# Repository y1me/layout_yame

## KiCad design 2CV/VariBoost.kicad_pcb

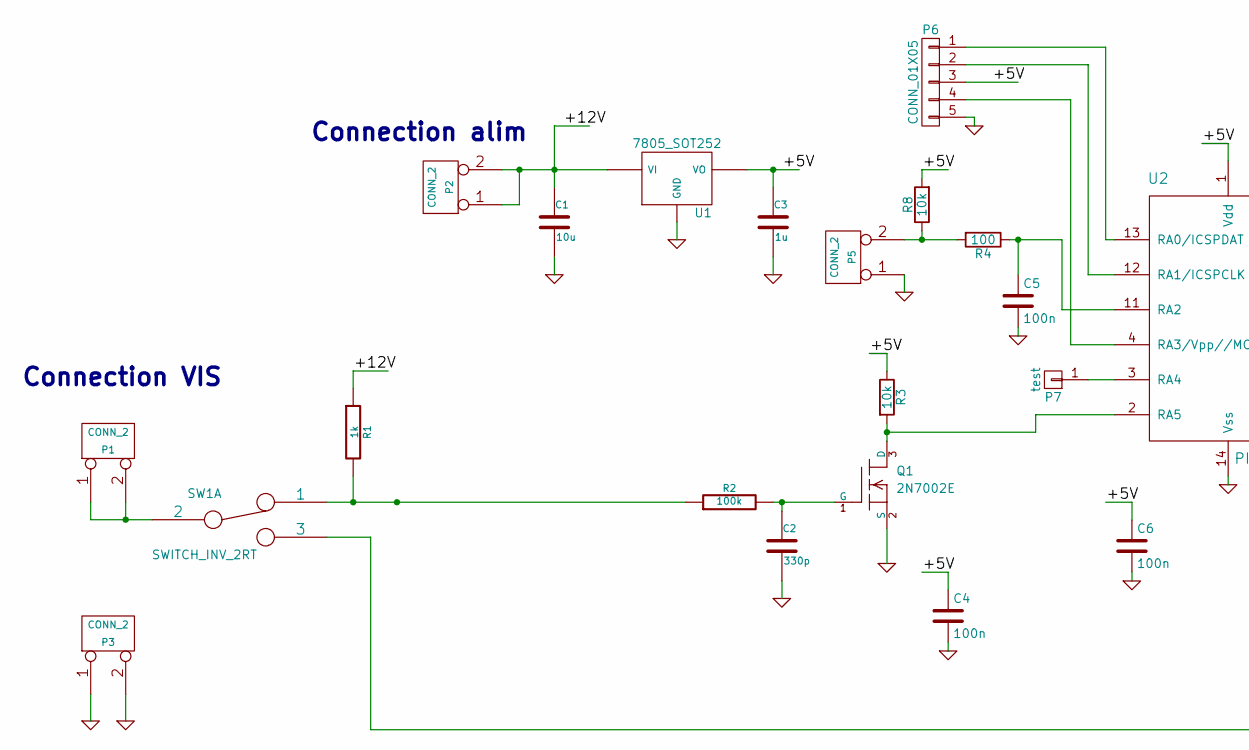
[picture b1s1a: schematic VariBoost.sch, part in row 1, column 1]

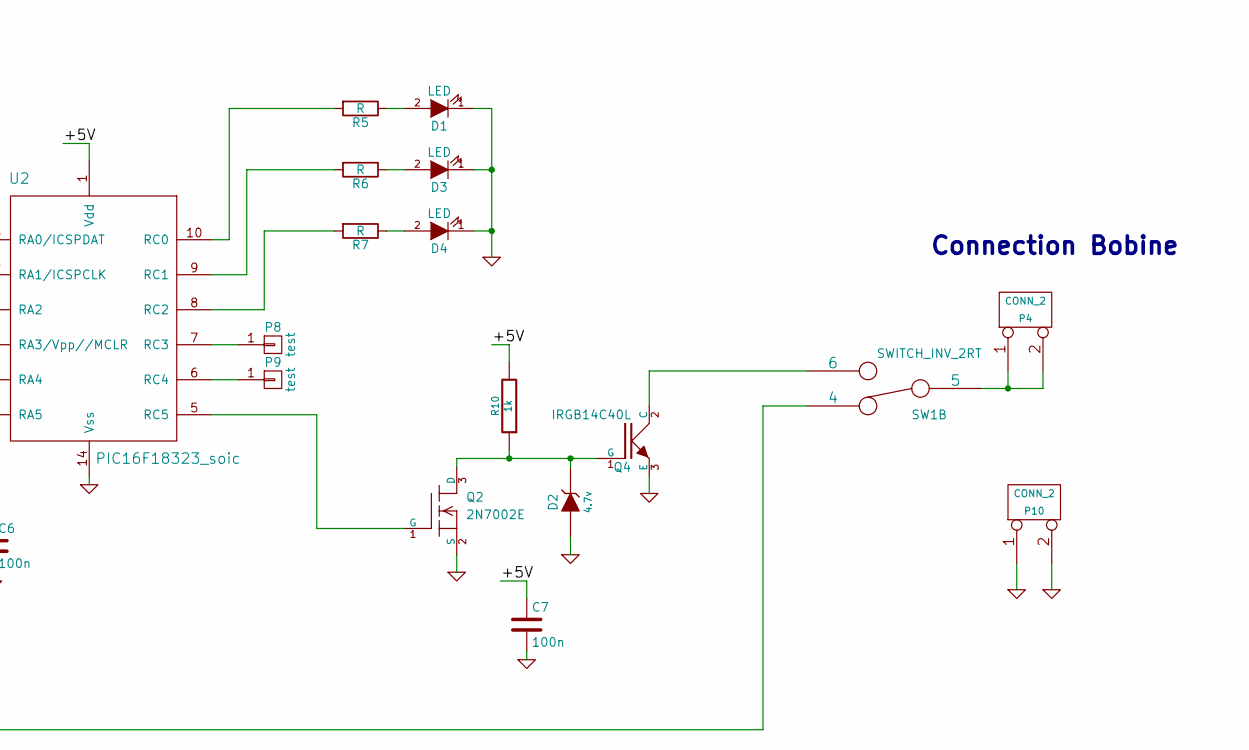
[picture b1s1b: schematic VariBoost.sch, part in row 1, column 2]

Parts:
C1: 10u; SM0805-MR
C2: 330p; SM0603-MR
C3: 1u; SM0603-MR
C4, C5, C6, C7: 100n; SM0603-MR
D1, D3, D4: LED; SM0603-LED-MR
D2: 4.7v; SOD-123
P1, P2, P3, P4, P5, P10: CONN_2; bornier2
P6: CONN_01X05; HE10_14-5C-2.54-MR
P7, P8, P9: test; Test_Point_T_H
Q1, Q2: 2N7002E; SOT23-MR
Q4: IRGB14C40L; TO-220_Neutral123_Vertical_LargePads
R1, R10: 1k; SM0603-MR
R2: 100k; SM0603-MR
R3, R8: 10k; SM0603-MR
R4: 100; SM0603-MR
R5, R6, R7: R; SM0603-MR
SW1: SWITCH_INV_2RT; SW_DPDT_2RT_5_08
U1: 7805_SOT252; TO-252-2Lead
U2: PIC16F18323_soic; SOIC-14_3.9x8.7mm_Pitch1.27mm

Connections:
/+5V: C3.1, C4.1, C6.1, C7.1, P6.3, R3.1, R8.2, R10.2, U1.3 (VO), U2.1 (Vdd)
/+12V: C1.1, P2.1, P2.2 (PM), R1.1, U1.1 (VI)
GND: C1.2, C2.2, C3.2, C4.2, C5.2, C6.2, C7.2, D1.1 (K), D2.1 (A), D3.1 (K), D4.1 (K), P3.1, P3.2 (PM), P5.1, P6.5, P10.1, P10.2 (PM), Q1.2 (S), Q2.2 (S), Q4.3 (E), U1.2 (GND), U2.14 (Vss); also elsewhere on the board
unnamed: C2.1, Q1.1 (G), R2.2
unnamed: C5.1, R4.1, U2.11 (RA2)
unnamed: D1.2 (A), R5.1
unnamed: D2.2 (K), Q2.3 (D), Q4.1 (G), R10.1
unnamed: D3.2 (A), R6.1
unnamed: D4.2 (A), R7.1
unnamed: P1.1, P1.2 (PM), SW1.2
unnamed: P4.1, P4.2 (PM), SW1.5
unnamed: P5.2 (PM), R4.2, R8.1
unnamed: P6.1, U2.13 (RA0/ICSPDAT)
unnamed: P6.2, U2.12 (RA1/ICSPCLK)
unnamed: P6.4, U2.4 (RA3/Vpp//MCLR)
unnamed: P7.1, U2.3 (RA4)
unnamed: P8.1, U2.7 (RC3)
unnamed: P9.1, U2.6 (RC4)
unnamed: Q1.3 (D), R3.2, U2.2 (RA5)
unnamed: Q2.1 (G), U2.5 (RC5)
unnamed: Q4.2 (C), SW1.6
unnamed: R1.2, R2.1, SW1.1
unnamed: R5.2, U2.10 (RC0)
unnamed: R6.2, U2.9 (RC1)
unnamed: R7.2, U2.8 (RC2)
unnamed: SW1.3, SW1.4

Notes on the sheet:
Connection alim
Connection VIS
Connection Bobine

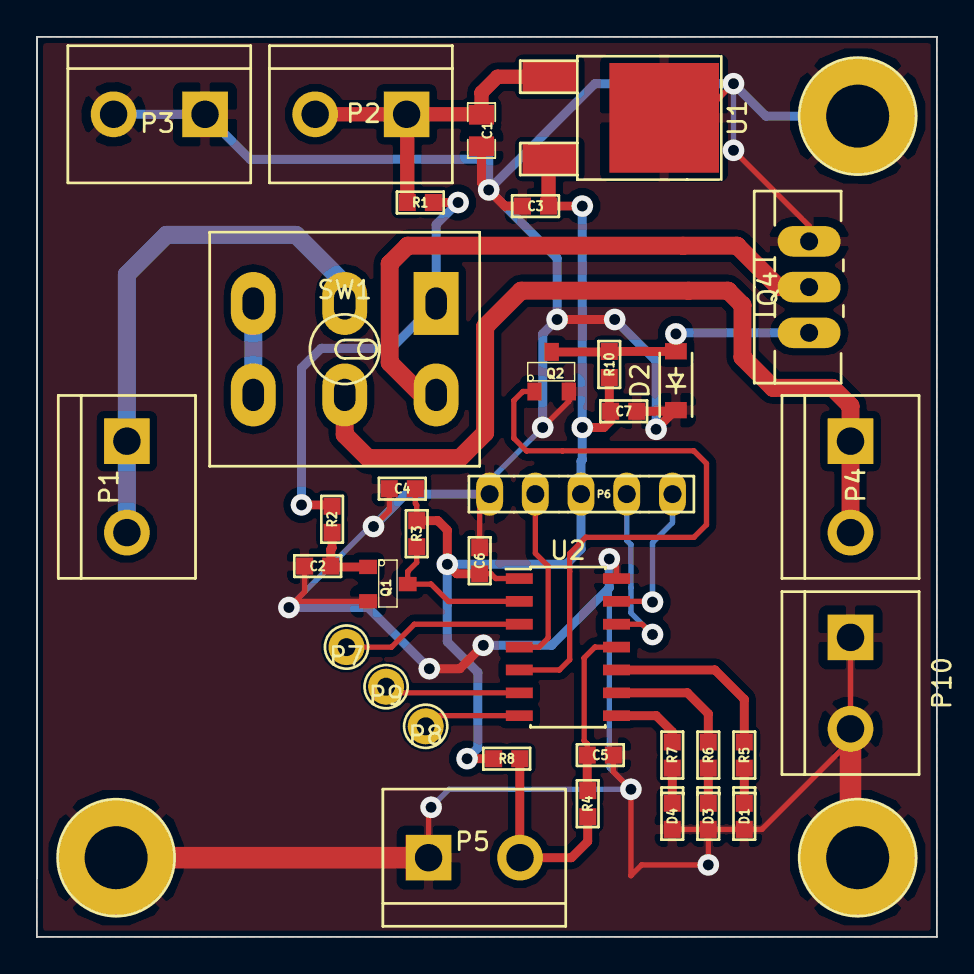
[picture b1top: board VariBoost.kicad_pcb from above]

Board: 2 copper layers, 50.0 x 50.0 mm, 39 parts (0 on the bottom side), 26 nets.

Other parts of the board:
MountingHole_3.5-6.5+GND, MountingHole_3.5-6.5+GND#2, MountingHole_3.5-6.5+GND#3: VAL**; MountingHole_3.5-6.5_GND

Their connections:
GND: MountingHole_3.5-6.5+GND.1, MountingHole_3.5-6.5+GND#2.1, MountingHole_3.5-6.5+GND#3.1; also elsewhere on the board

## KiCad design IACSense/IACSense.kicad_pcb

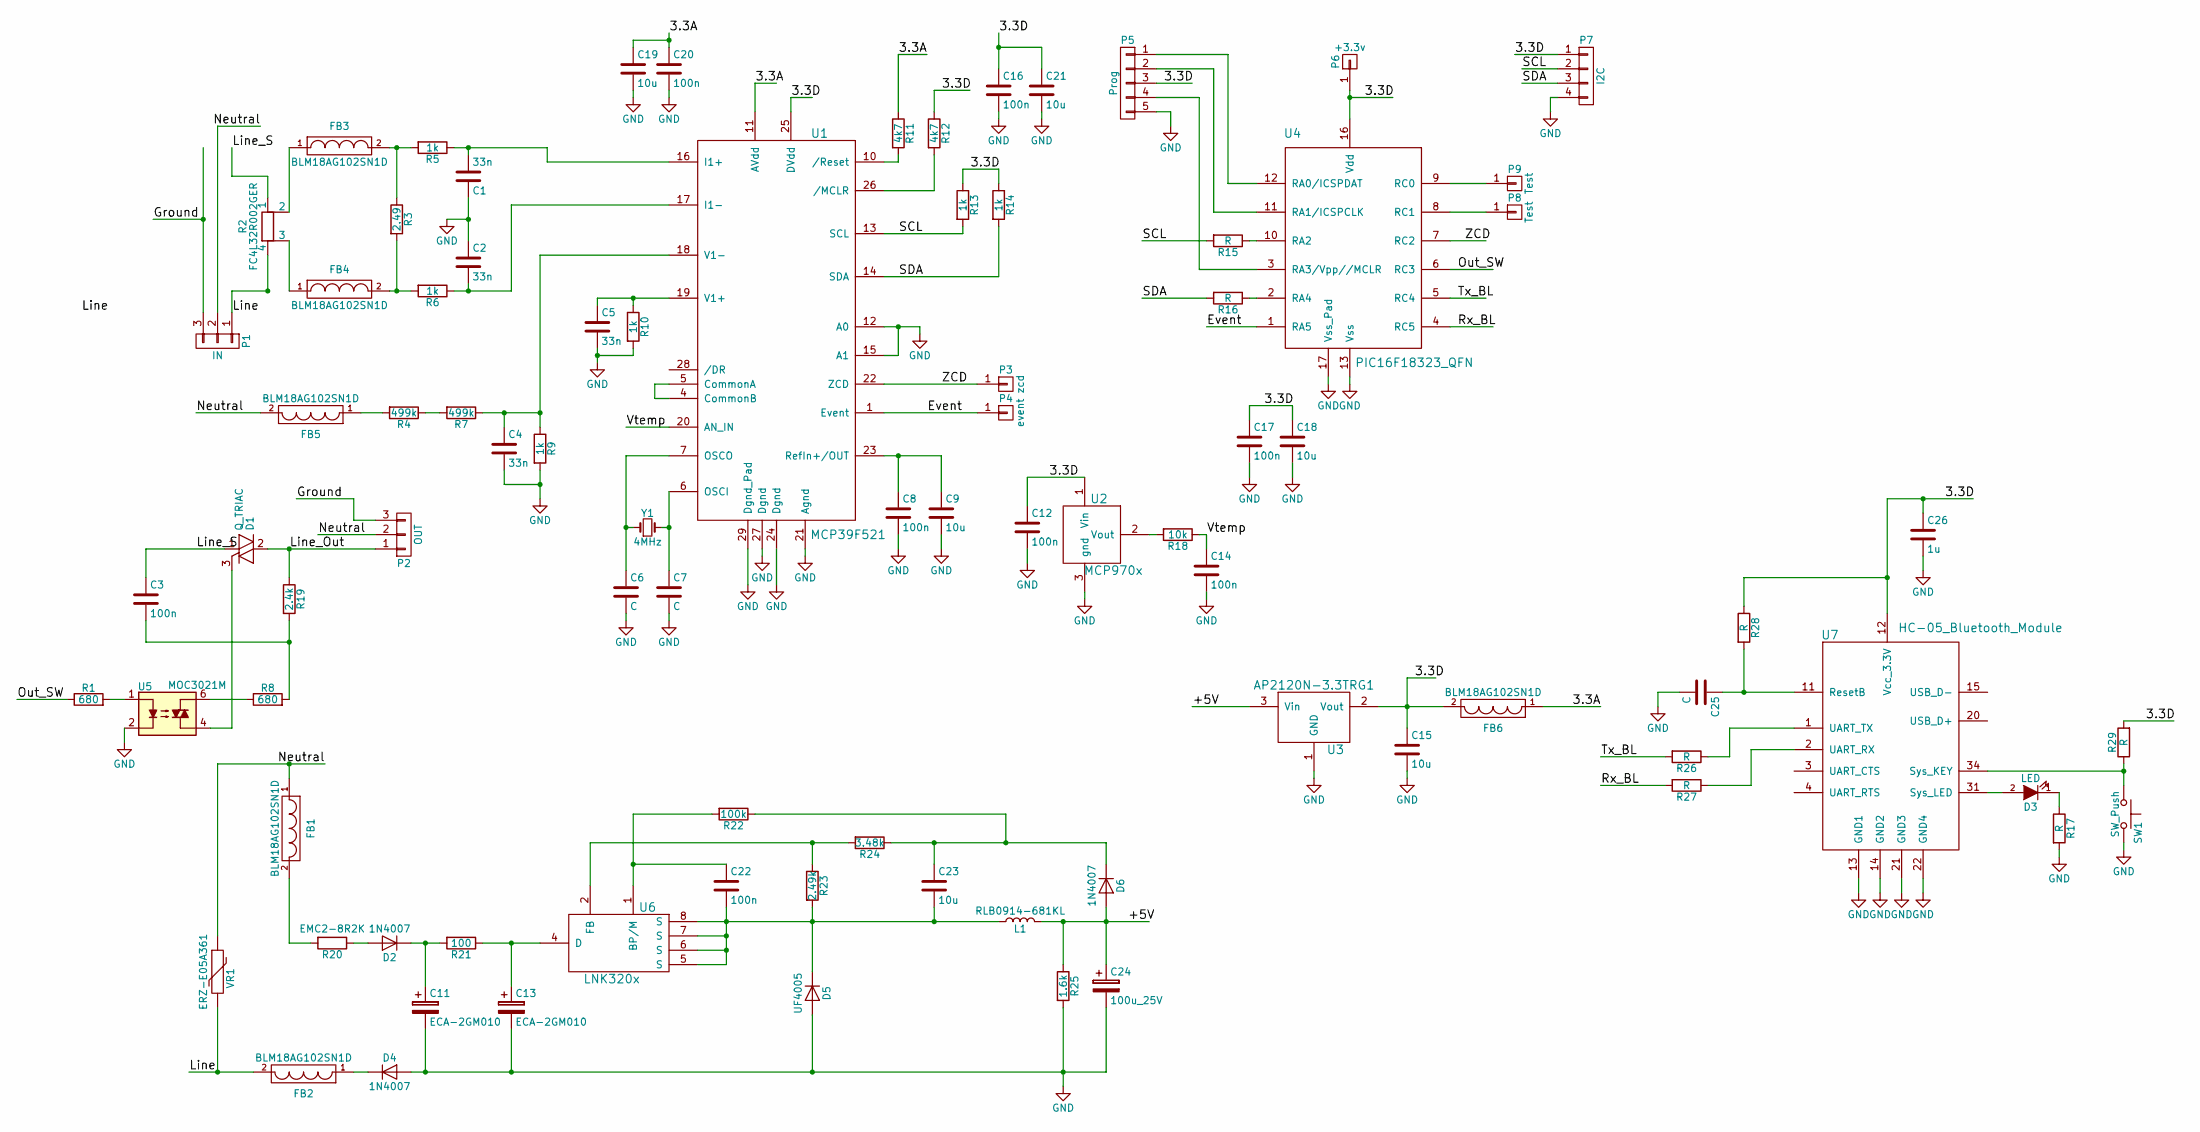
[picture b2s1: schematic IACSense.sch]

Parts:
C1, C2, C4, C5: 33n; SM0603-MR
C3: 100n; C_Rect_L13.0mm_W6.0mm_P10.00mm_FKS3_FKP3_MKS4
C6, C7, C25: C; SM0603-MR
C8, C12, C14, C16, C17, C20, C22: 100n; SM0603-MR
C9, C15, C18, C19, C21, C23: 10u; SM0805-MR
C11, C13: ECA-2GM010; CP_Radial_D6.3mm_P2.50mm
C24: 100u_25V; CP_Radial_D6.3mm_P2.50mm
C26: 1u; SM0805-MR
D1: Q_TRIAC; TO-220-3_Vertical
D2, D4, D6: 1N4007; D_DO-41_SOD81_P7.62mm_Horizontal
D3: LED; SM0603-LED-MR
D5: UF4005; D_DO-41_SOD81_P7.62mm_Horizontal
FB1, FB2, FB3, FB4, FB5, FB6: BLM18AG102SN1D; SM0603-MR
L1: RLB0914-681KL; L_Radial_D8.7mm_P5.00mm_Fastron_07HCP
P1: IN; Conn3_Term
P2: OUT; Conn3_Term
P3: zcd; Pin_Header_Straight_1x01_Pitch1.00mm
P4: event; Pin_Header_Straight_1x01_Pitch1.00mm
P5: Prog; Pin_Header_Straight_1x05_Pitch2.54mm
P6: +3.3v; Pin_Header_Straight_1x01_Pitch1.00mm
P7: I2C; Pin_Header_Straight_1x04_Pitch1.27mm
P8, P9: Test; Pin_Header_Straight_1x01_Pitch1.00mm
R1: 680; SM0603-MR
R2: FC4L32R002GER; FC4L32
R3: 2.49; SM0603-MR
R4, R7: 499k; SM0603-MR
R5, R6, R9, R10, R13, R14: 1k; SM0603-MR
R8: 680; R_Axial_DIN0414_L11.9mm_D4.5mm_P5.08mm_Vertical
R11, R12: 4k7; SM0603-MR
R15, R16: R; SM0201-MR
R17, R26, R27, R28, R29: R; SM0603-MR
R18: 10k; SM0603-MR
R19: 2.4k; R_Axial_DIN0414_L11.9mm_D4.5mm_P5.08mm_Vertical
R20: EMC2-8R2K; R_Axial_DIN0414_L11.9mm_D4.5mm_P5.08mm_Vertical
R21: 100; SM0805-MR
R22: 100k; SM0603-MR
R23: 2.49k; SM0603-MR
R24: 3.48k; SM0603-MR
R25: 1.6k; SM0603-MR
SW1: SW_Push; SW_SPST_FSMSM
U1: MCP39F521; QFN-28-1EP_5x5mm_Pitch0.5mm
U2: MCP970x; SOT23-MR
U3: AP2120N-3.3TRG1; SOT23-MR
U4: PIC16F18323_QFN; QFN-16-1EP_4x4mm_Pitch0.65mm
U5: MOC3021M; DIP-6_W7.62mm
U6: LNK320x; SO-8C-7
U7: HC-05_Bluetooth_Module; HM-10_BLE
VR1: ERZ-E05A361; VR_5mm
Y1: 4MHz; Crystal_HC49-4H_Vertical

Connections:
/3.3A: C19.1, C20.1, FB6.1, R11.1, U1.11 (AVdd)
/3.3D: C12.1, C15.1, C16.1, C17.1, C18.1, C21.1, C26.1, FB6.2, P5.3, P6.1, P7.1, R12.1, R13.1, R14.1, R28.1, R29.2, U1.25 (DVdd), U2.1 (Vin), U3.2 (Vout), U4.16 (Vdd), U7.12 (Vcc_3.3V)
/+5V: C24.1, D6.2 (A), L1.2, R25.1, U3.3 (Vin)
/Event: P4.1, U1.1 (Event), U4.1 (RA5)
/Ground: P1.3, P2.3
/Line: FB2.2, P1.1, R2.4, VR1.2
/Line_Out: D1.2 (A1), P2.1, R19.1
/Line_S: C3.1, D1.1 (A2), R2.1
/Neutral: FB1.1, FB5.2, P1.2, P2.2, VR1.1
/Out_SW: R1.1, U4.6 (RC3)
/Rx_BL: R27.2, U4.4 (RC5)
/SCL: P7.2, R13.2, R15.2, U1.13 (SCL)
/SDA: P7.3, R14.2, R16.2, U1.14 (SDA)
/Tx_BL: R26.2, U4.5 (RC4)
/Vtemp: C14.1, R18.1, U1.20 (AN_IN)
/ZCD: P3.1, U1.22 (ZCD), U4.7 (RC2)
GND: C1.1, C2.1, C4.2, C5.2, C6.2, C7.2, C8.2, C9.2, C11.2, C12.2, C13.2, C14.2, C15.2, C16.2, C17.2, C18.2, C19.2, C20.2, C21.2, C24.2, C25.2, C26.2, D4.2 (A), D5.2 (A), P5.5, P7.4, R9.2, R10.2, R17.2, R25.2, SW1.2, U1.12 (A0), U1.15 (A1), U1.21 (Agnd), U1.24 (Dgnd), U1.27 (Dgnd), U1.29 (Dgnd_Pad), U2.3 (gnd), U3.1 (GND), U4.13 (Vss), U4.17 (Vss_Pad), U5.2, U7.13 (GND1), U7.14 (GND2), U7.21 (GND3), U7.22 (GND4)
unnamed: C1.2, R5.1, U1.16 (I1+)
unnamed: C2.2, R6.1, U1.17 (I1-)
unnamed: C3.2, R8.2, R19.2
unnamed: C4.1, R7.1, R9.1, U1.18 (V1-)
unnamed: C5.1, R10.1, U1.19 (V1+)
unnamed: C6.1, U1.7 (OSCO), Y1.1
unnamed: C7.1, U1.6 (OSCI), Y1.2
unnamed: C8.1, C9.1, U1.23 (RefIn+/OUT)
unnamed: C11.1, D2.1 (K), R21.2
unnamed: C13.1, R21.1, U6.4 (D)
unnamed: C22.1, R22.2, U6.1 (BP/M)
unnamed: C22.2, C23.2, D5.1 (K), L1.1, R23.2, U6.5 (S), U6.6 (S), U6.7 (S), U6.8 (S)
unnamed: C23.1, D6.1 (K), R22.1, R24.1
unnamed: C25.1, R28.2, U7.11 (ResetB)
unnamed: D1.3 (G), U5.4
unnamed: D2.2 (A), R20.1
unnamed: D3.1 (K), R17.1
unnamed: D3.2 (A), U7.31 (Sys_LED)
unnamed: D4.1 (K), FB2.1
unnamed: FB1.2, R20.2
unnamed: FB3.1, R2.2
unnamed: FB3.2, R3.1, R5.2
unnamed: FB4.1, R2.3
unnamed: FB4.2, R3.2, R6.2
unnamed: FB5.1, R4.2
unnamed: P5.1, U4.12 (RA0/ICSPDAT)
unnamed: P5.2, U4.11 (RA1/ICSPCLK)
unnamed: P5.4, U4.3 (RA3/Vpp//MCLR)
unnamed: P8.1, U4.8 (RC1)
unnamed: P9.1, U4.9 (RC0)
unnamed: R1.2, U5.1
unnamed: R4.1, R7.2
unnamed: R8.1, U5.6
unnamed: R11.2, U1.10 (/Reset)
unnamed: R12.2, U1.26 (/MCLR)
unnamed: R15.1, U4.10 (RA2)
unnamed: R16.1, U4.2 (RA4)
unnamed: R18.2, U2.2 (Vout)
unnamed: R23.1, R24.2, U6.2 (FB)
unnamed: R26.1, U7.1 (UART_TX)
unnamed: R27.1, U7.2 (UART_RX)
unnamed: R29.1, SW1.1, U7.34 (Sys_KEY)
unnamed: U1.4 (CommonB), U1.5 (CommonA)

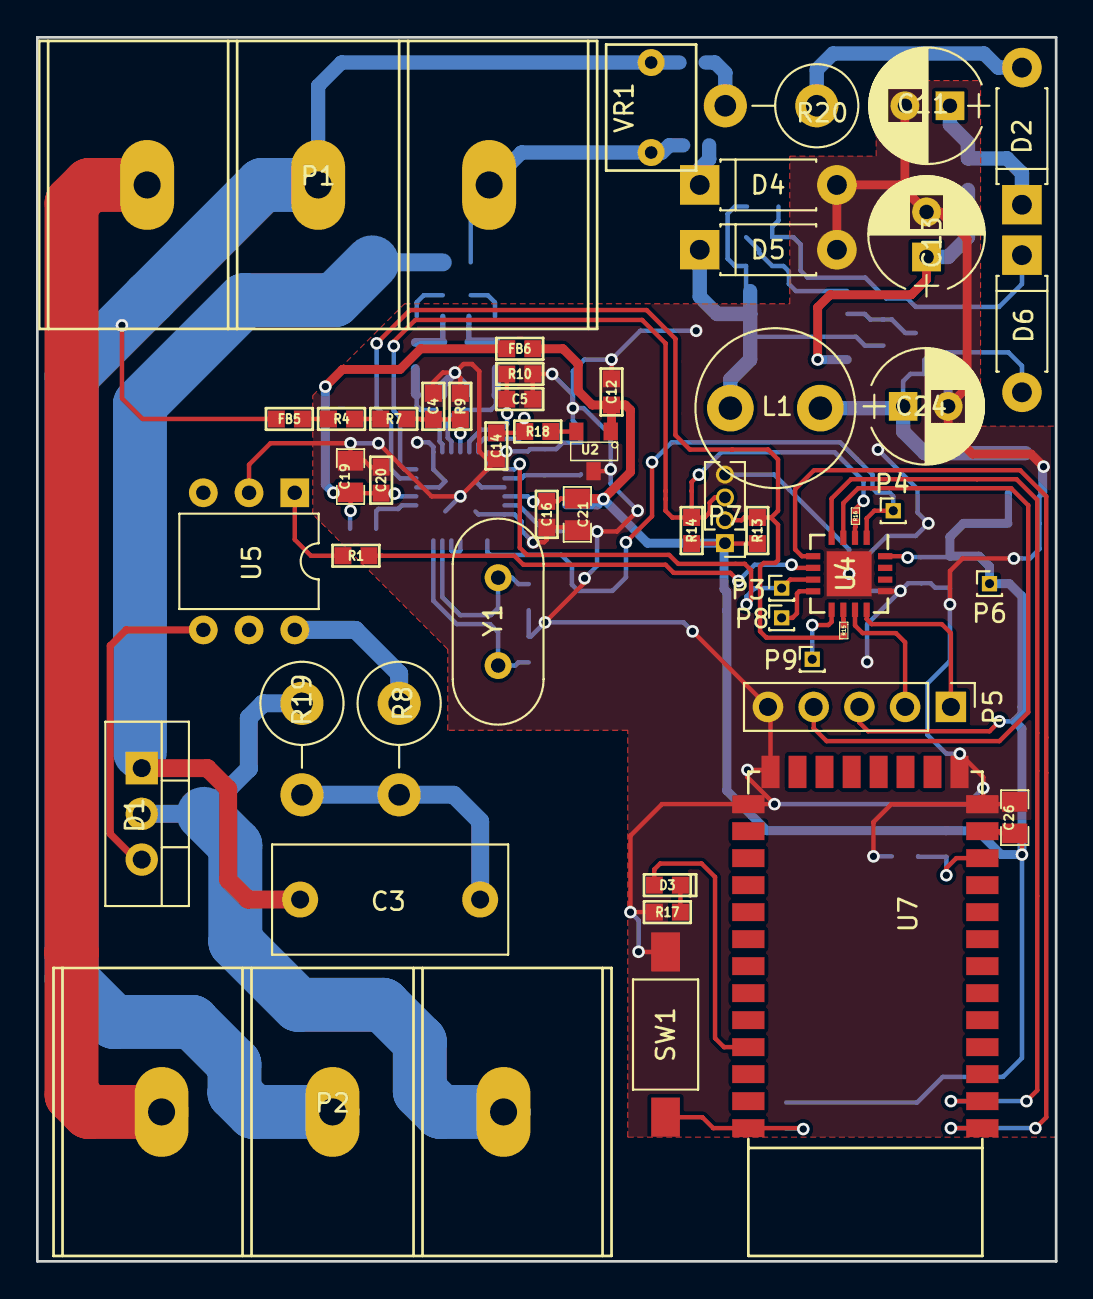
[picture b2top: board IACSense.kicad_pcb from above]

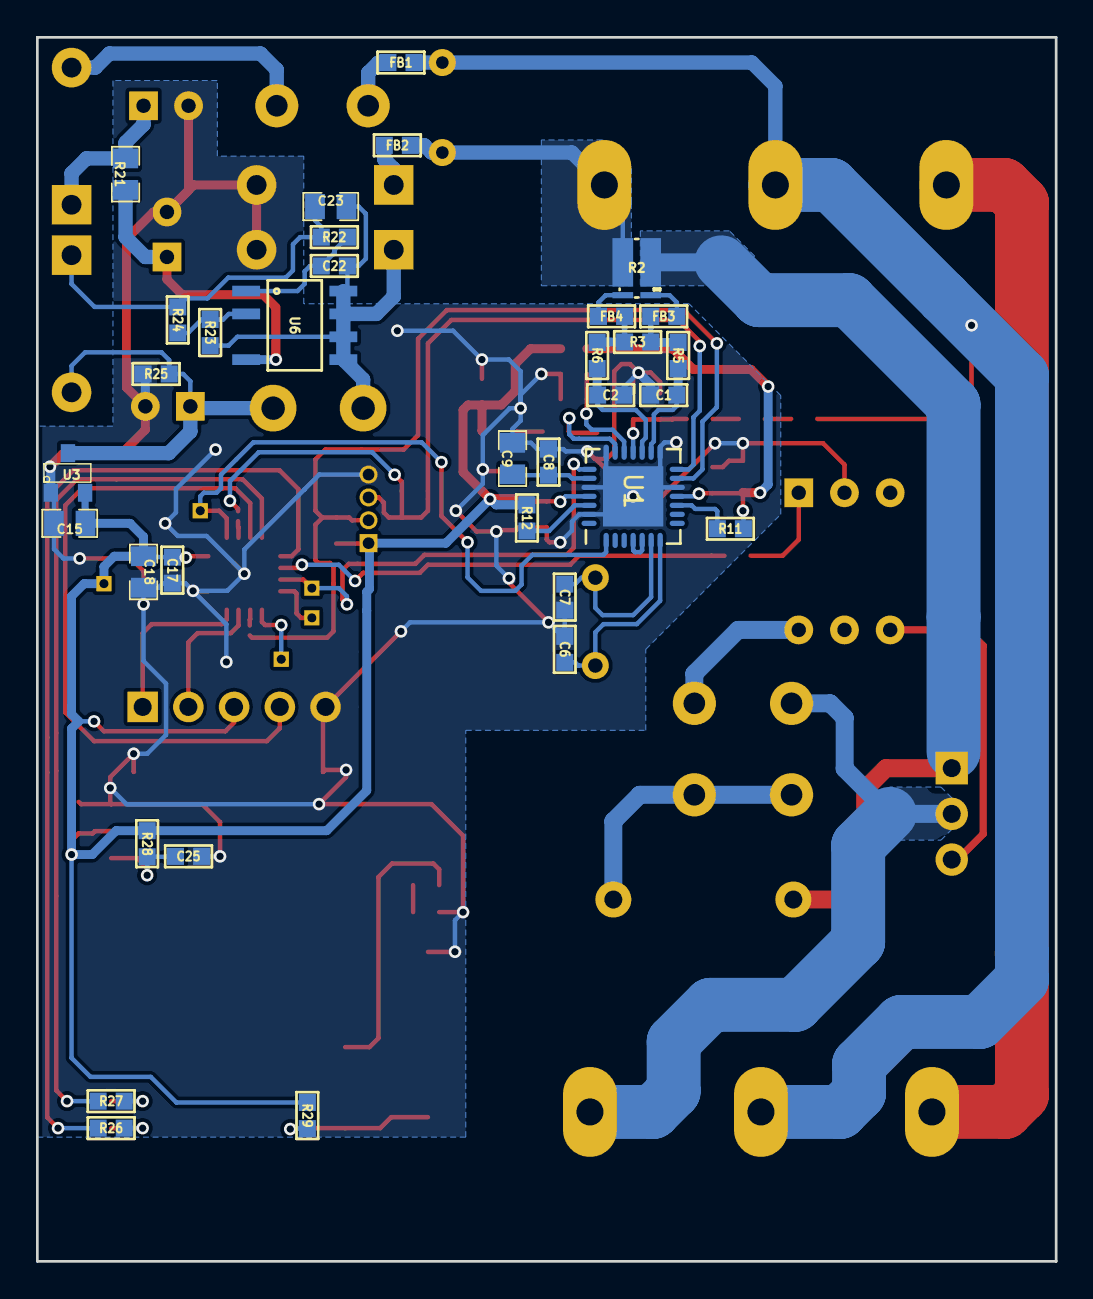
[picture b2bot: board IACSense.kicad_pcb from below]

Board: 2 copper layers, 56.6 x 68.0 mm, 86 parts (34 on the bottom side), 60 nets.
